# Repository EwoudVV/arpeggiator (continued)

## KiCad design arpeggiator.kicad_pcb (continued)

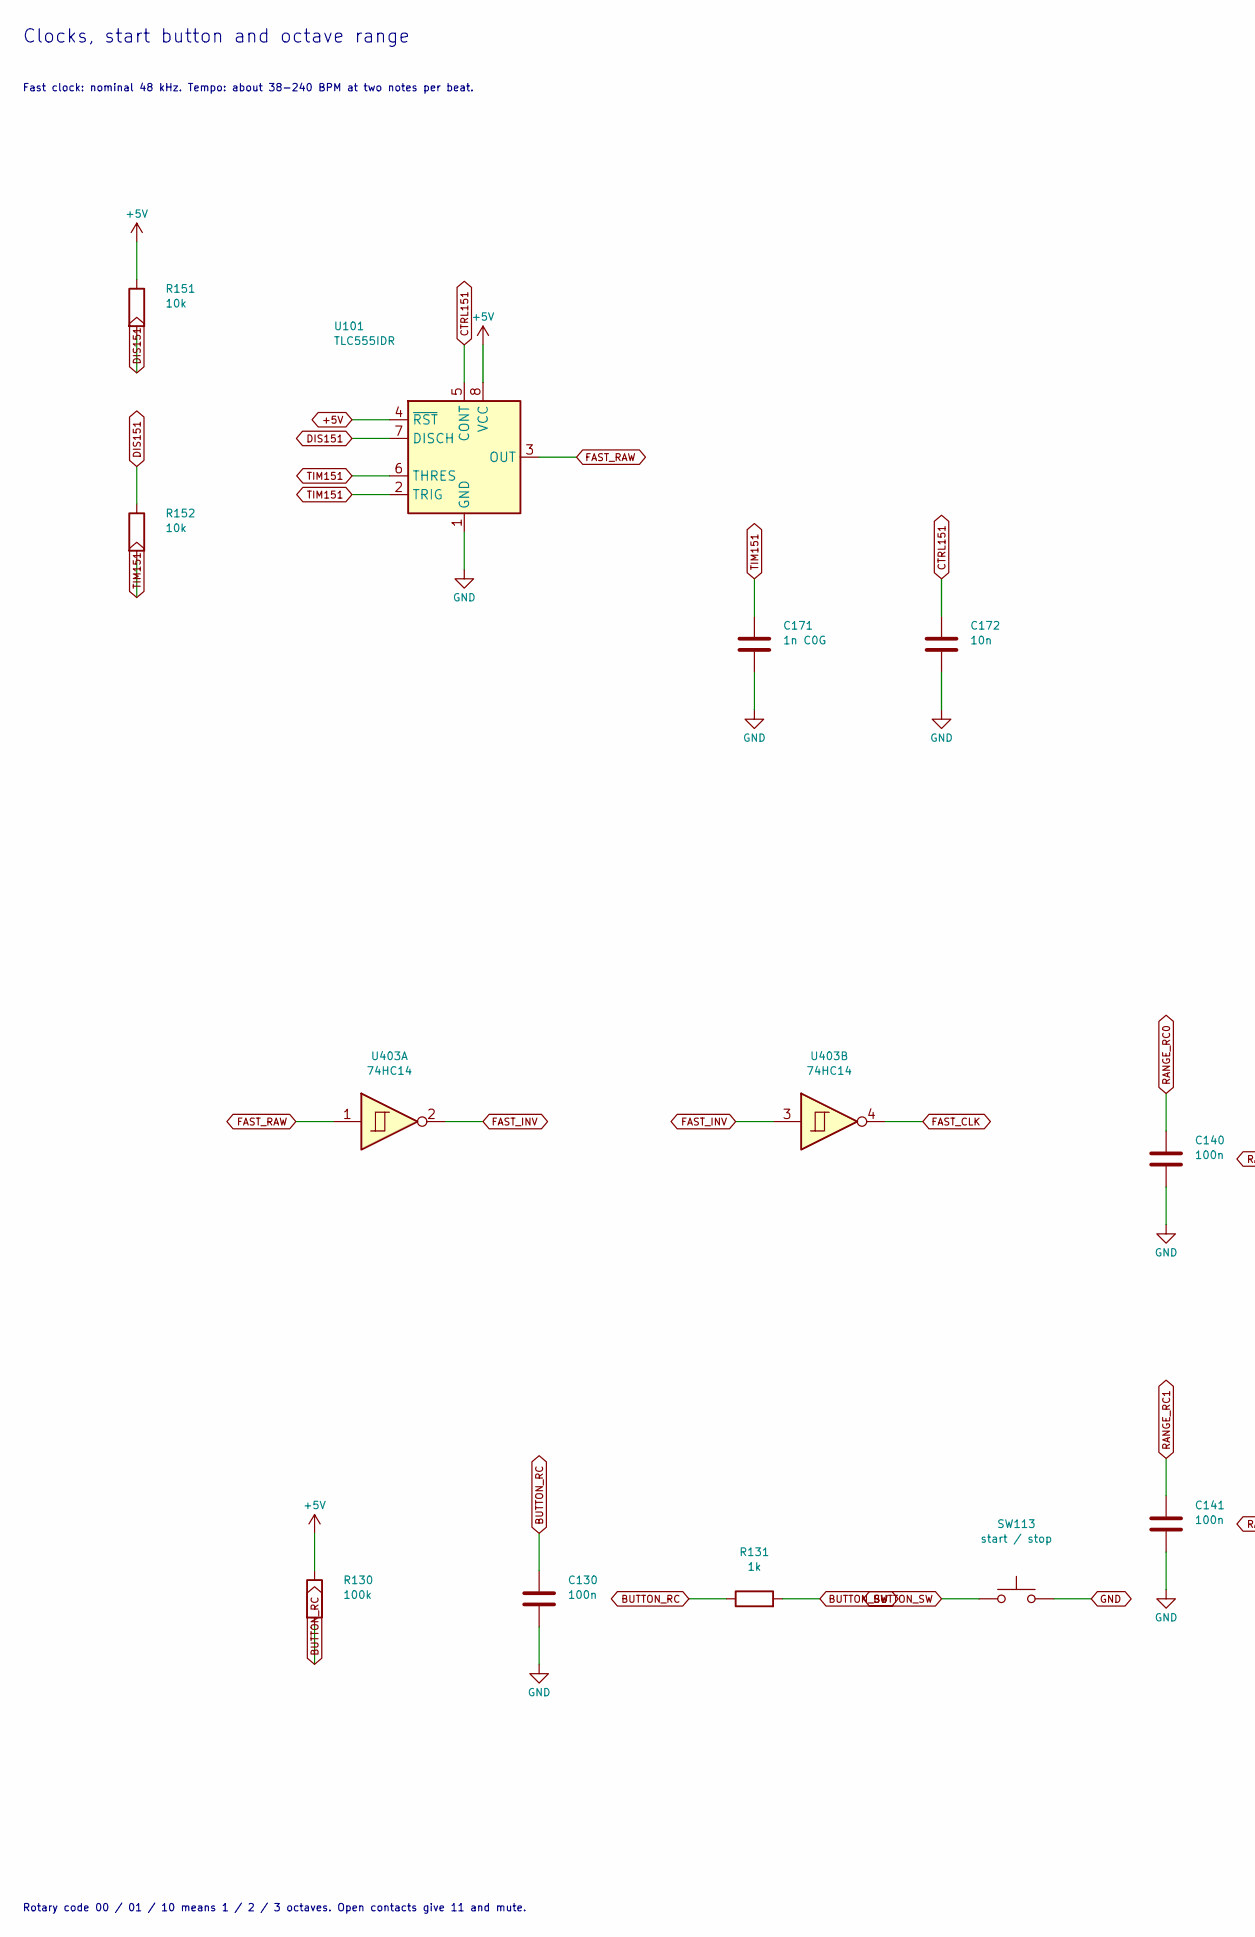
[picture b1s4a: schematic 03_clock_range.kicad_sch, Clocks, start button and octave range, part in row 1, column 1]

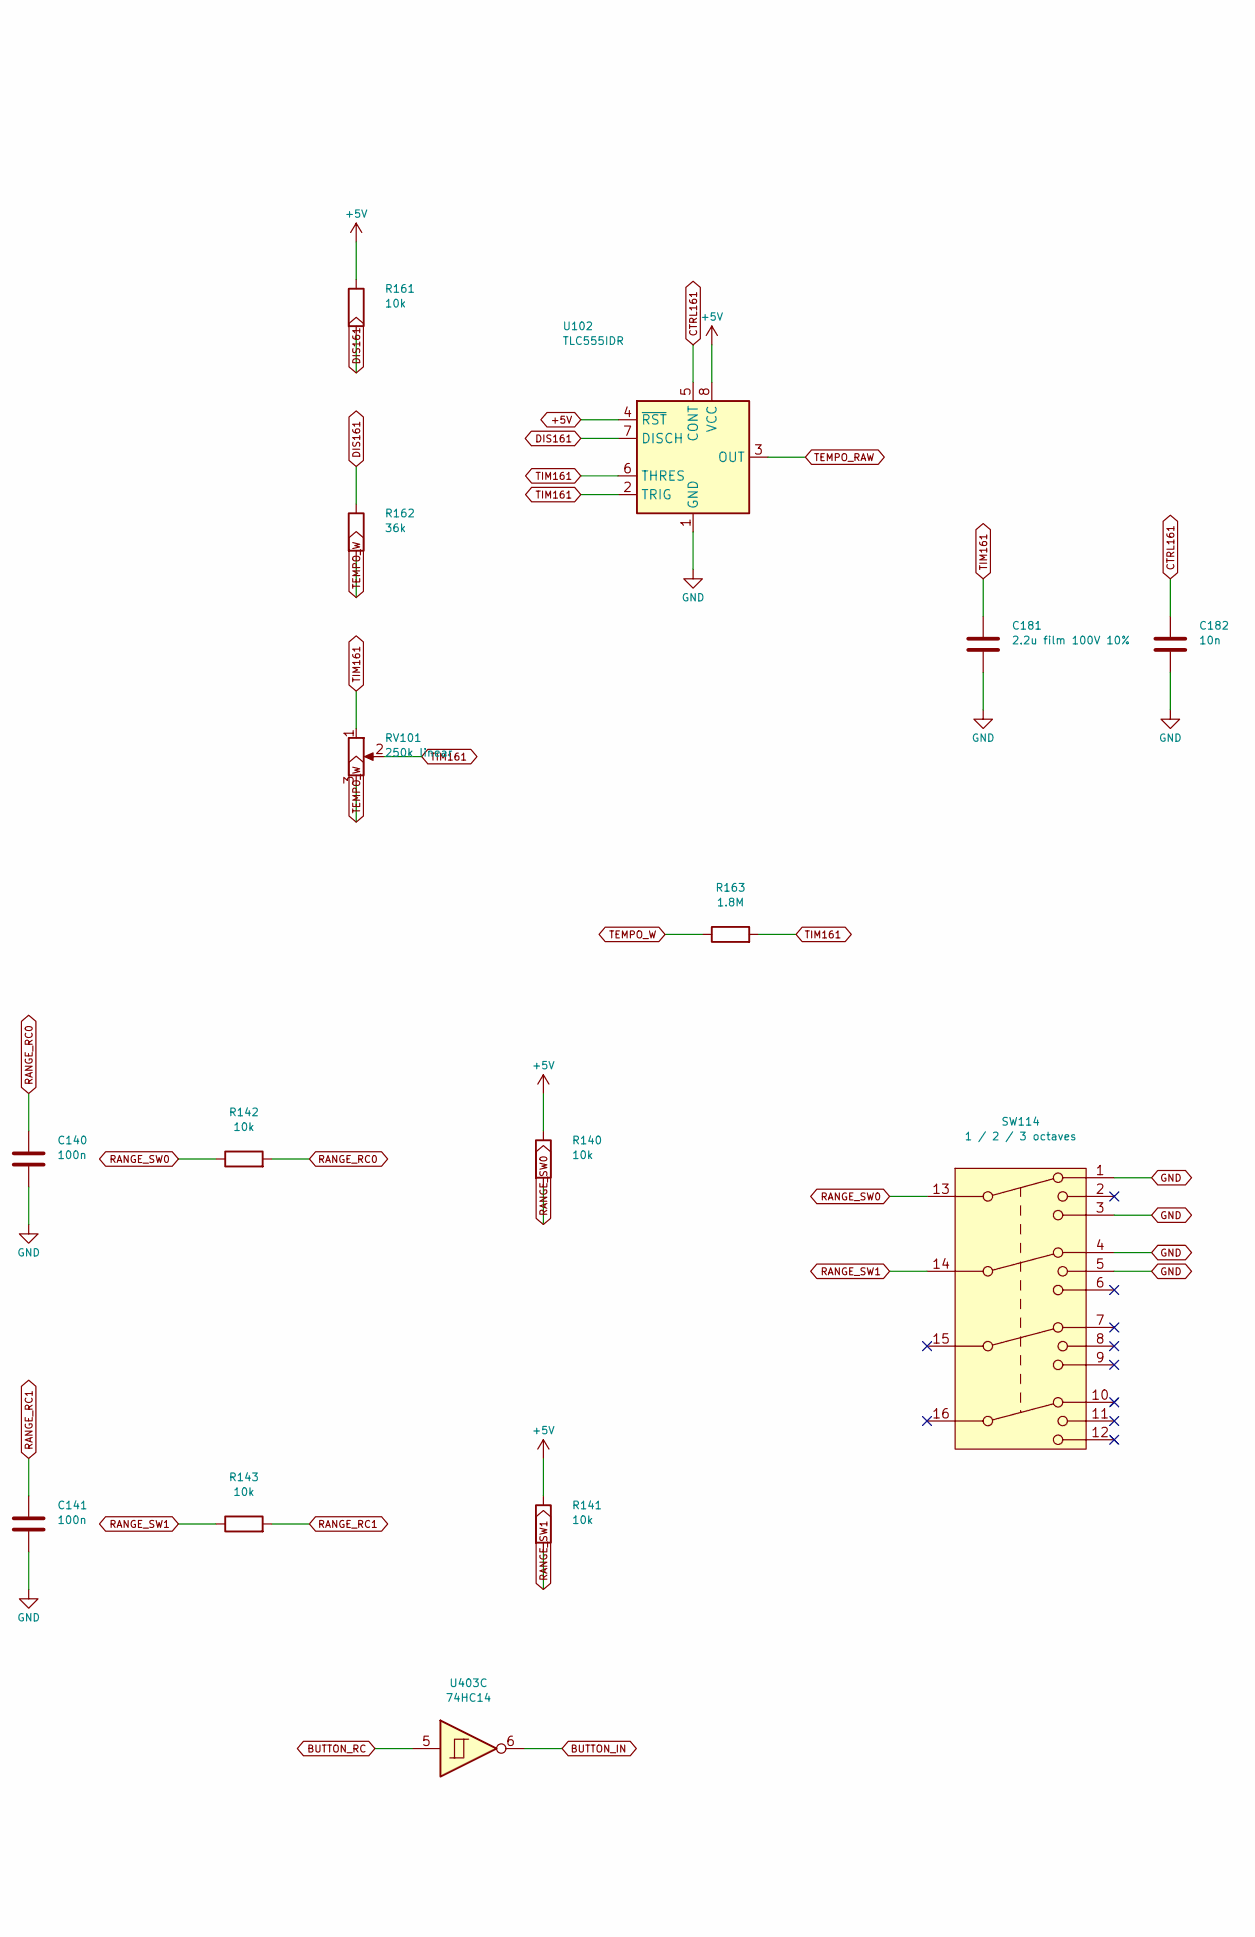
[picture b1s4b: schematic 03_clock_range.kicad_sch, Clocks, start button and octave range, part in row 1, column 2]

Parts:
C130, C140, C141: 100n; C_0805_2012Metric
C171: 1n C0G; C_0805_2012Metric
C172, C182: 10n; C_0805_2012Metric
C181: 2.2u film 100V 10%; C_Rect_L18.0mm_W8.0mm_P15.00mm_FKS3_FKP3; MPN MKS4D042204F00KSSD
R130: 100k; R_0805_2012Metric
R131: 1k; R_0805_2012Metric
R140, R141, R142, R143, R151, R152, R161: 10k; R_0805_2012Metric
R162: 36k; R_0805_2012Metric
R163: 1.8M; R_0805_2012Metric
RV101: 250k linear; Potentiometer_Alpha_RD901F-40-00D_Single_Vertical; MPN RD901F-40-15F-B250K
SW113: start / stop; SW_SPST_Omron_B3F-40xx; MPN B3F-4055
SW114: 1 / 2 / 3 octaves; SW_Alpha_SR2612F_4P3T; MPN SR2612F-0403-18R0B-D8-N
U101, U102: TLC555IDR; SOIC-8_3.9x4.9mm_P1.27mm; MPN TLC555IDR
U403: 74HC14; SOIC-14_3.9x8.7mm_P1.27mm; MPN 74HC14D,653

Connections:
+5V: R130.1, R140.1, R141.1, R151.1, R161.1, U101.4 (~RST), U101.8 (VCC), U102.4 (~RST), U102.8 (VCC); also elsewhere on the board
BUTTON_IN: U403.6; also elsewhere on the board
BUTTON_RC: C130.1, R130.2, R131.1, U403.5
BUTTON_SW: R131.2, SW113.1
CTRL151: C172.1, U101.5 (CONT)
CTRL161: C182.1, U102.5 (CONT)
DIS151: R151.2, R152.1, U101.7 (DISCH)
DIS161: R161.2, R162.1, U102.7 (DISCH)
FAST_CLK: U403.4; also elsewhere on the board
FAST_INV: U403.2, U403.3
FAST_RAW: U101.3 (OUT), U403.1
RANGE_RC0: C140.1, R142.2; also elsewhere on the board
RANGE_RC1: C141.1, R143.2; also elsewhere on the board
RANGE_SW0: R140.2, R142.1, SW114.13
RANGE_SW1: R141.2, R143.1, SW114.14
TEMPO_RAW: U102.3 (OUT); also elsewhere on the board
TEMPO_W: R162.2, R163.1, RV101.3
TIM151: C171.1, R152.2, U101.2 (TRIG), U101.6 (THRES)
TIM161: C181.1, R163.2, RV101.1, RV101.2, U102.2 (TRIG), U102.6 (THRES)

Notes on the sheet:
Clocks, start button and octave range
Fast clock: nominal 48 kHz. Tempo: about 38-240 BPM at two notes per beat.
Rotary code 00 / 01 / 10 means 1 / 2 / 3 octaves. Open contacts give 11 and mute.

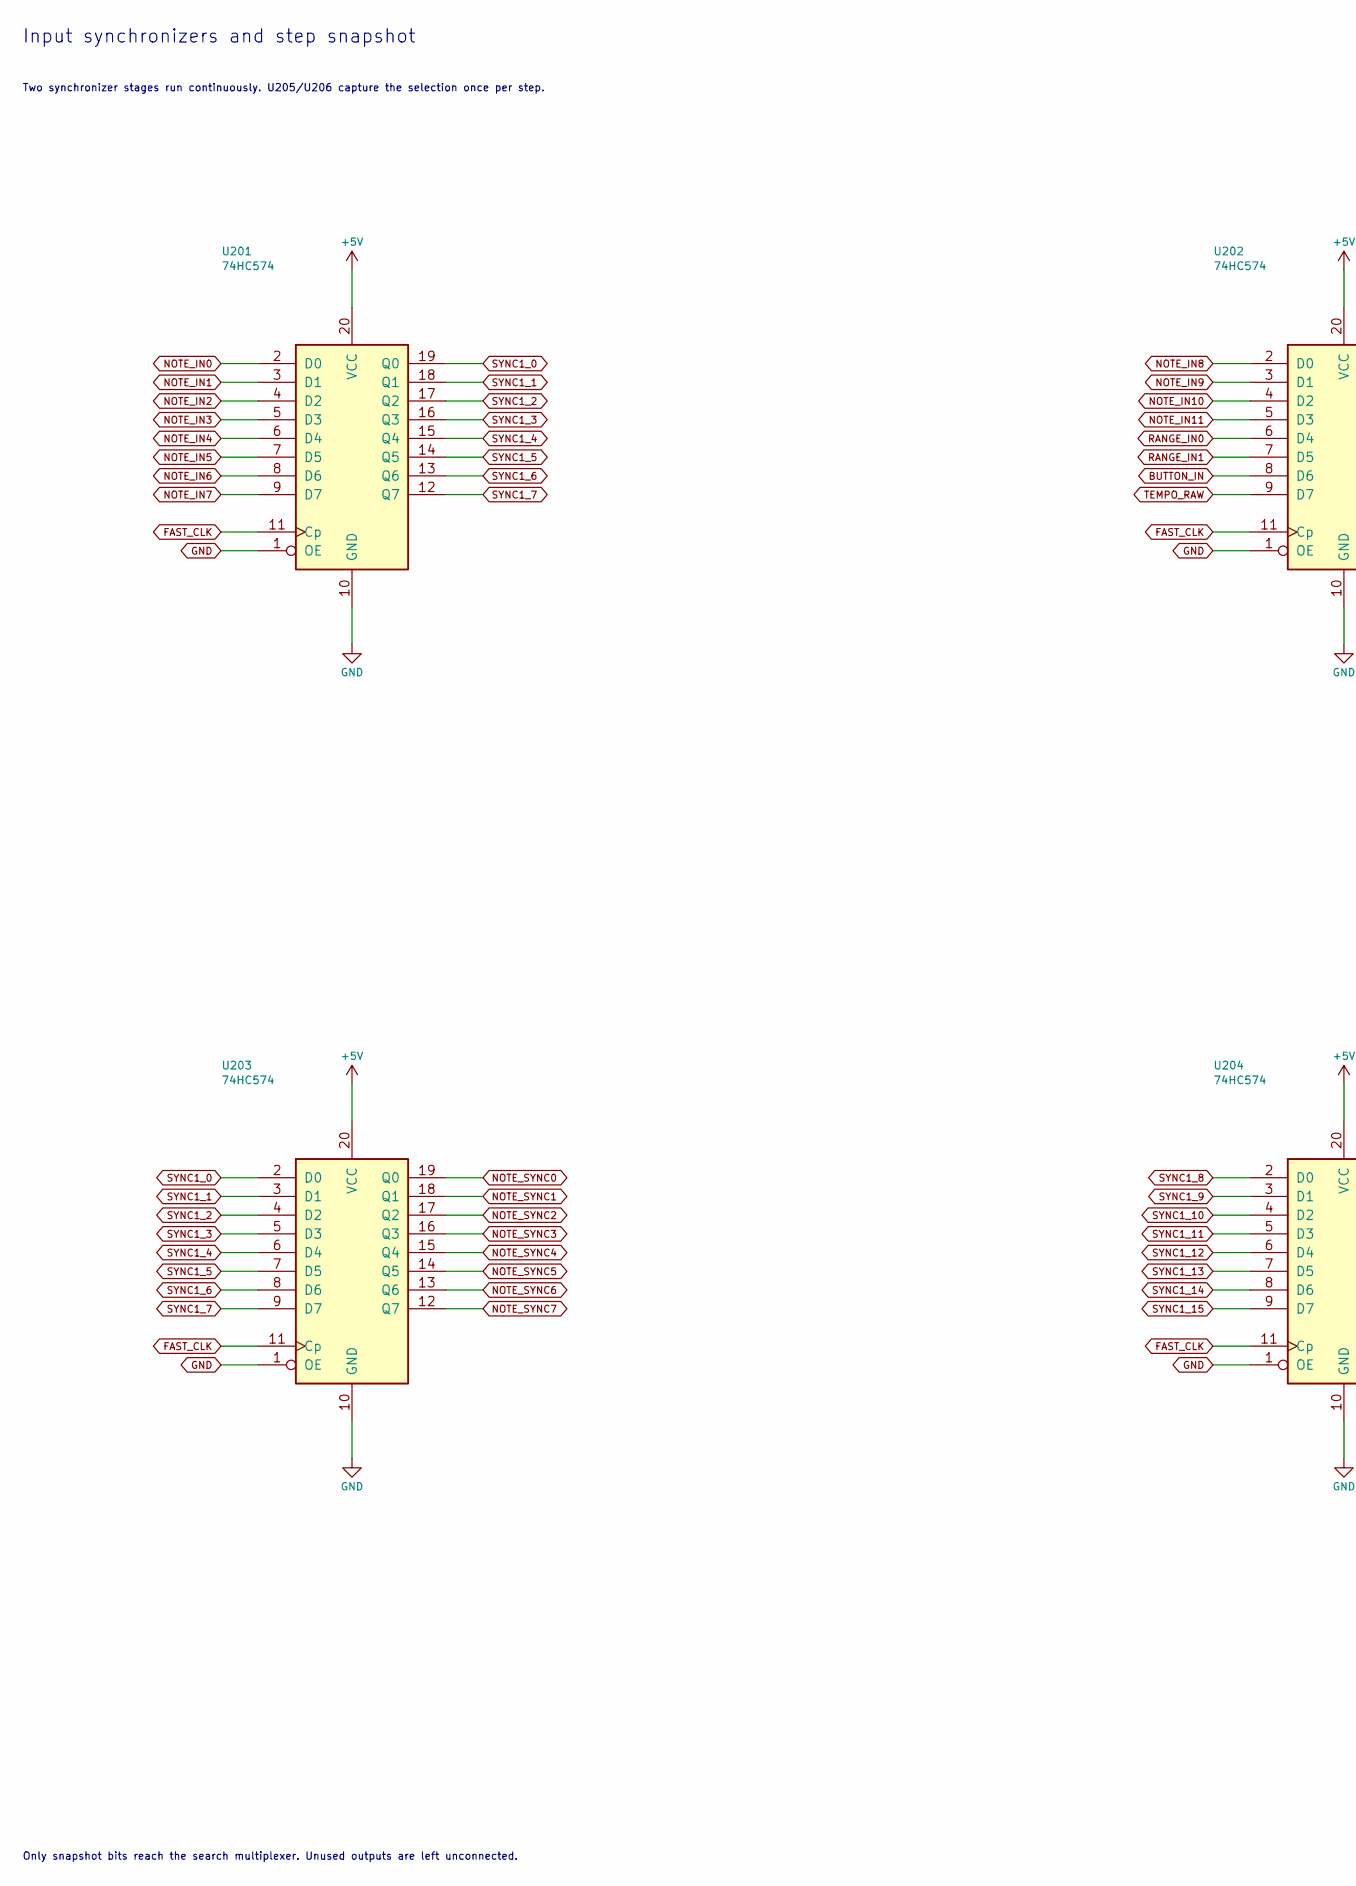
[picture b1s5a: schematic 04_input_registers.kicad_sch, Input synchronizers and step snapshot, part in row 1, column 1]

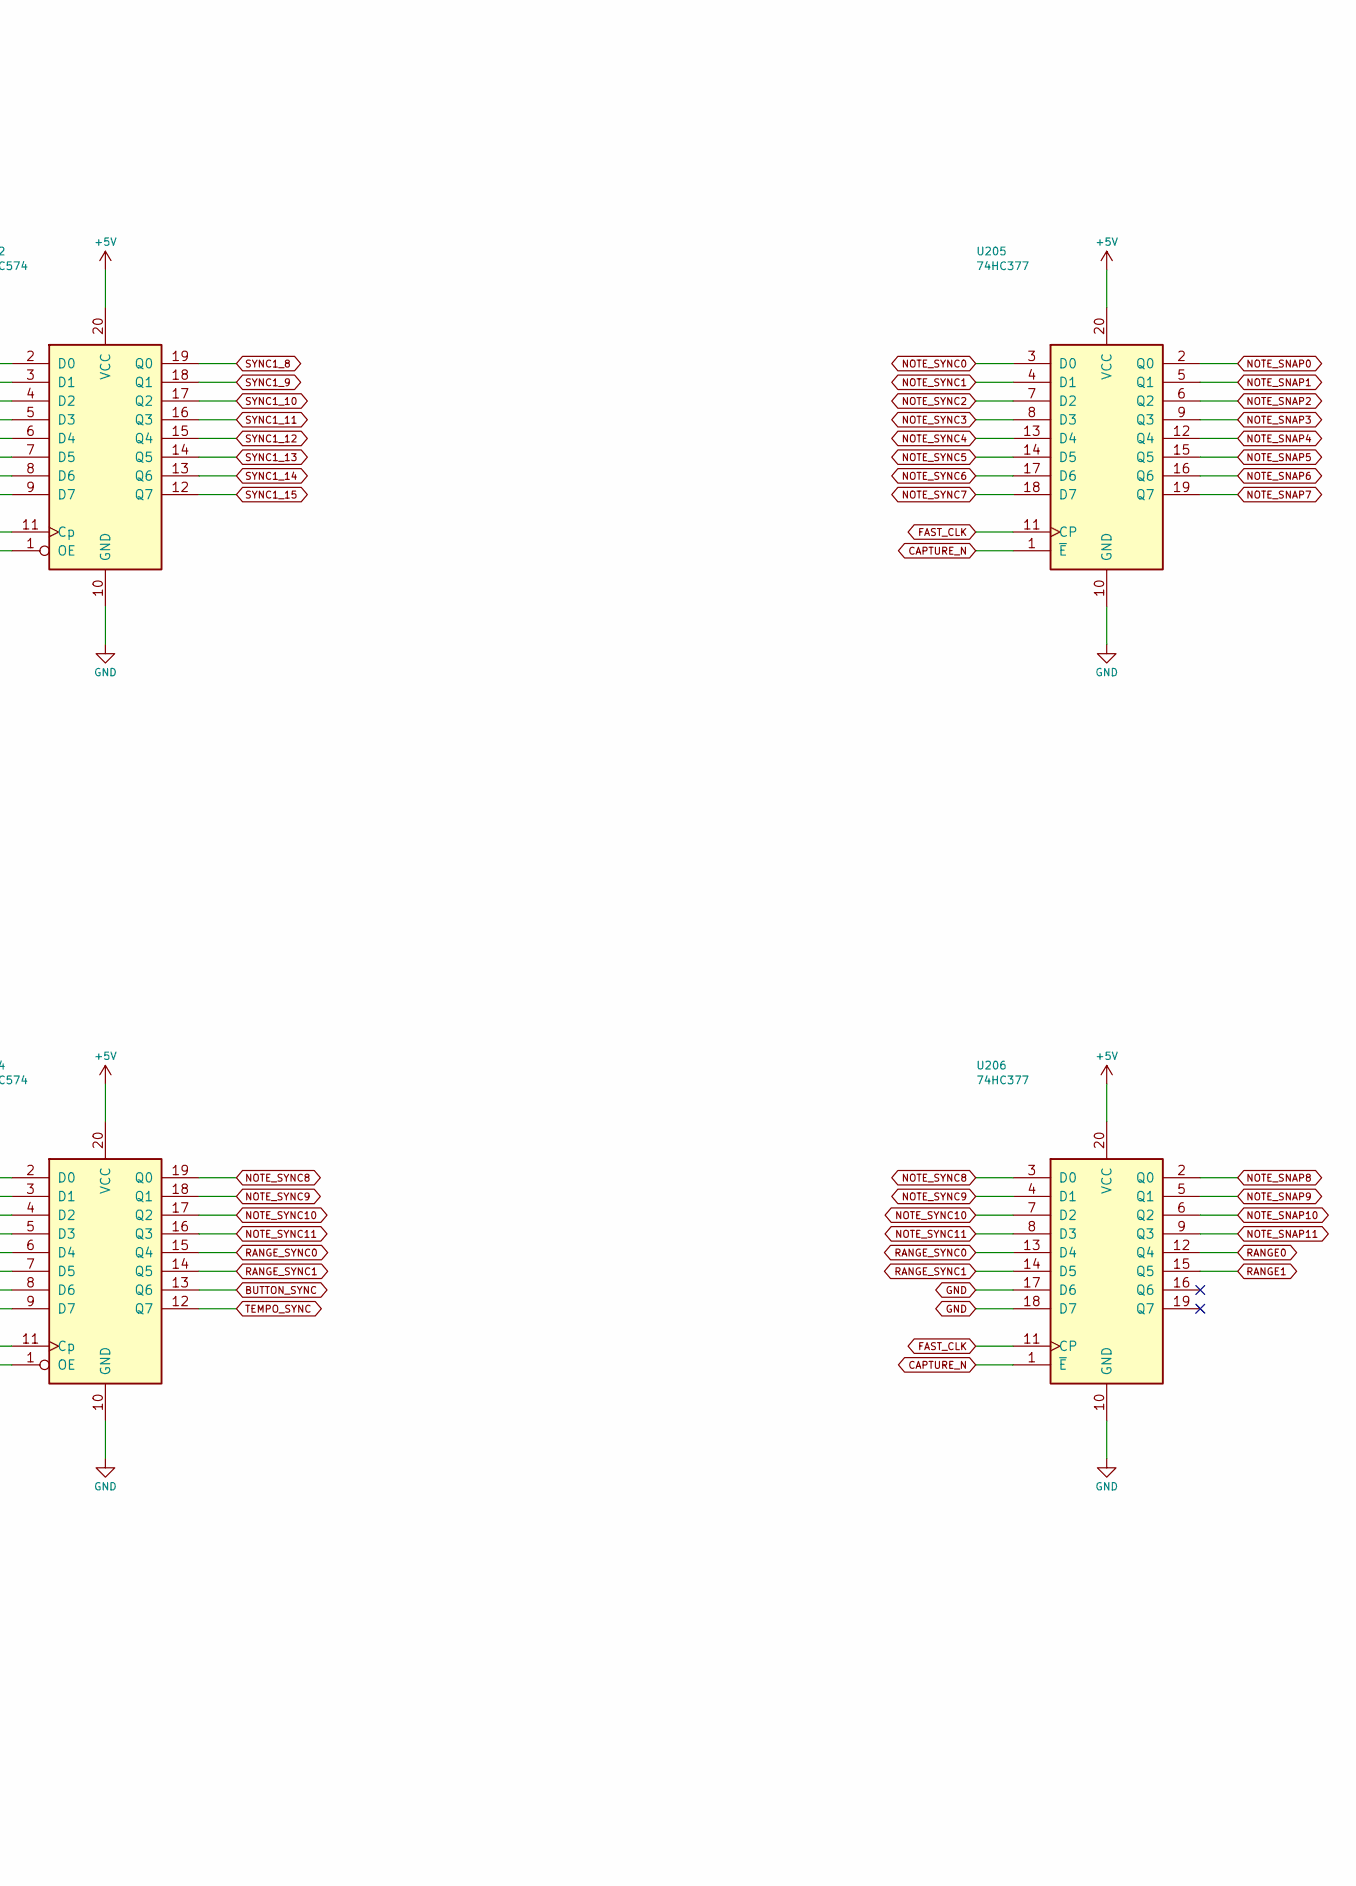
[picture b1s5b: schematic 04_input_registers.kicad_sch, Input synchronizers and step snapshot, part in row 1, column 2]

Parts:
U201, U202, U203, U204: 74HC574; SOIC-20W_7.5x12.8mm_P1.27mm; MPN 74HC574D,653
U205, U206: 74HC377; SOIC-20W_7.5x12.8mm_P1.27mm; MPN 74HC377D,653

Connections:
+5V: U201.20 (VCC), U202.20 (VCC), U203.20 (VCC), U204.20 (VCC), U205.20 (VCC), U206.20 (VCC); also elsewhere on the board
BUTTON_IN: U202.8 (D6); also elsewhere on the board
BUTTON_SYNC: U204.13 (Q6); also elsewhere on the board
CAPTURE_N: U205.1 (~E), U206.1 (~E); also elsewhere on the board
FAST_CLK: U201.11 (Cp), U202.11 (Cp), U203.11 (Cp), U204.11 (Cp), U205.11 (CP), U206.11 (CP); also elsewhere on the board
NOTE_IN0: U201.2 (D0); also elsewhere on the board
NOTE_IN1: U201.3 (D1); also elsewhere on the board
NOTE_IN2: U201.4 (D2); also elsewhere on the board
NOTE_IN3: U201.5 (D3); also elsewhere on the board
NOTE_IN4: U201.6 (D4); also elsewhere on the board
NOTE_IN5: U201.7 (D5); also elsewhere on the board
NOTE_IN6: U201.8 (D6); also elsewhere on the board
NOTE_IN7: U201.9 (D7); also elsewhere on the board
NOTE_IN8: U202.2 (D0); also elsewhere on the board
NOTE_IN9: U202.3 (D1); also elsewhere on the board
NOTE_IN10: U202.4 (D2); also elsewhere on the board
NOTE_IN11: U202.5 (D3); also elsewhere on the board
NOTE_SNAP0: U205.2 (Q0); also elsewhere on the board
NOTE_SNAP1: U205.5 (Q1); also elsewhere on the board
NOTE_SNAP2: U205.6 (Q2); also elsewhere on the board
NOTE_SNAP3: U205.9 (Q3); also elsewhere on the board
NOTE_SNAP4: U205.12 (Q4); also elsewhere on the board
NOTE_SNAP5: U205.15 (Q5); also elsewhere on the board
NOTE_SNAP6: U205.16 (Q6); also elsewhere on the board
NOTE_SNAP7: U205.19 (Q7); also elsewhere on the board
NOTE_SNAP8: U206.2 (Q0); also elsewhere on the board
NOTE_SNAP9: U206.5 (Q1); also elsewhere on the board
NOTE_SNAP10: U206.6 (Q2); also elsewhere on the board
NOTE_SNAP11: U206.9 (Q3); also elsewhere on the board
NOTE_SYNC0: U203.19 (Q0), U205.3 (D0)
NOTE_SYNC1: U203.18 (Q1), U205.4 (D1)
NOTE_SYNC2: U203.17 (Q2), U205.7 (D2)
NOTE_SYNC3: U203.16 (Q3), U205.8 (D3)
NOTE_SYNC4: U203.15 (Q4), U205.13 (D4)
NOTE_SYNC5: U203.14 (Q5), U205.14 (D5)
NOTE_SYNC6: U203.13 (Q6), U205.17 (D6)
NOTE_SYNC7: U203.12 (Q7), U205.18 (D7)
NOTE_SYNC8: U204.19 (Q0), U206.3 (D0)
NOTE_SYNC9: U204.18 (Q1), U206.4 (D1)
NOTE_SYNC10: U204.17 (Q2), U206.7 (D2)
NOTE_SYNC11: U204.16 (Q3), U206.8 (D3)
RANGE0: U206.12 (Q4); also elsewhere on the board
RANGE1: U206.15 (Q5); also elsewhere on the board
RANGE_IN0: U202.6 (D4); also elsewhere on the board
RANGE_IN1: U202.7 (D5); also elsewhere on the board
RANGE_SYNC0: U204.15 (Q4), U206.13 (D4)
RANGE_SYNC1: U204.14 (Q5), U206.14 (D5)
SYNC1_0: U201.19 (Q0), U203.2 (D0)
SYNC1_1: U201.18 (Q1), U203.3 (D1)
SYNC1_2: U201.17 (Q2), U203.4 (D2)
SYNC1_3: U201.16 (Q3), U203.5 (D3)
SYNC1_4: U201.15 (Q4), U203.6 (D4)
SYNC1_5: U201.14 (Q5), U203.7 (D5)
SYNC1_6: U201.13 (Q6), U203.8 (D6)
SYNC1_7: U201.12 (Q7), U203.9 (D7)
SYNC1_8: U202.19 (Q0), U204.2 (D0)
SYNC1_9: U202.18 (Q1), U204.3 (D1)
SYNC1_10: U202.17 (Q2), U204.4 (D2)
SYNC1_11: U202.16 (Q3), U204.5 (D3)
SYNC1_12: U202.15 (Q4), U204.6 (D4)
SYNC1_13: U202.14 (Q5), U204.7 (D5)
SYNC1_14: U202.13 (Q6), U204.8 (D6)
SYNC1_15: U202.12 (Q7), U204.9 (D7)
TEMPO_RAW: U202.9 (D7); also elsewhere on the board
TEMPO_SYNC: U204.12 (Q7); also elsewhere on the board

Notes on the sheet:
Input synchronizers and step snapshot
Two synchronizer stages run continuously. U205/U206 capture the selection once per step.
Only snapshot bits reach the search multiplexer. Unused outputs are left unconnected.

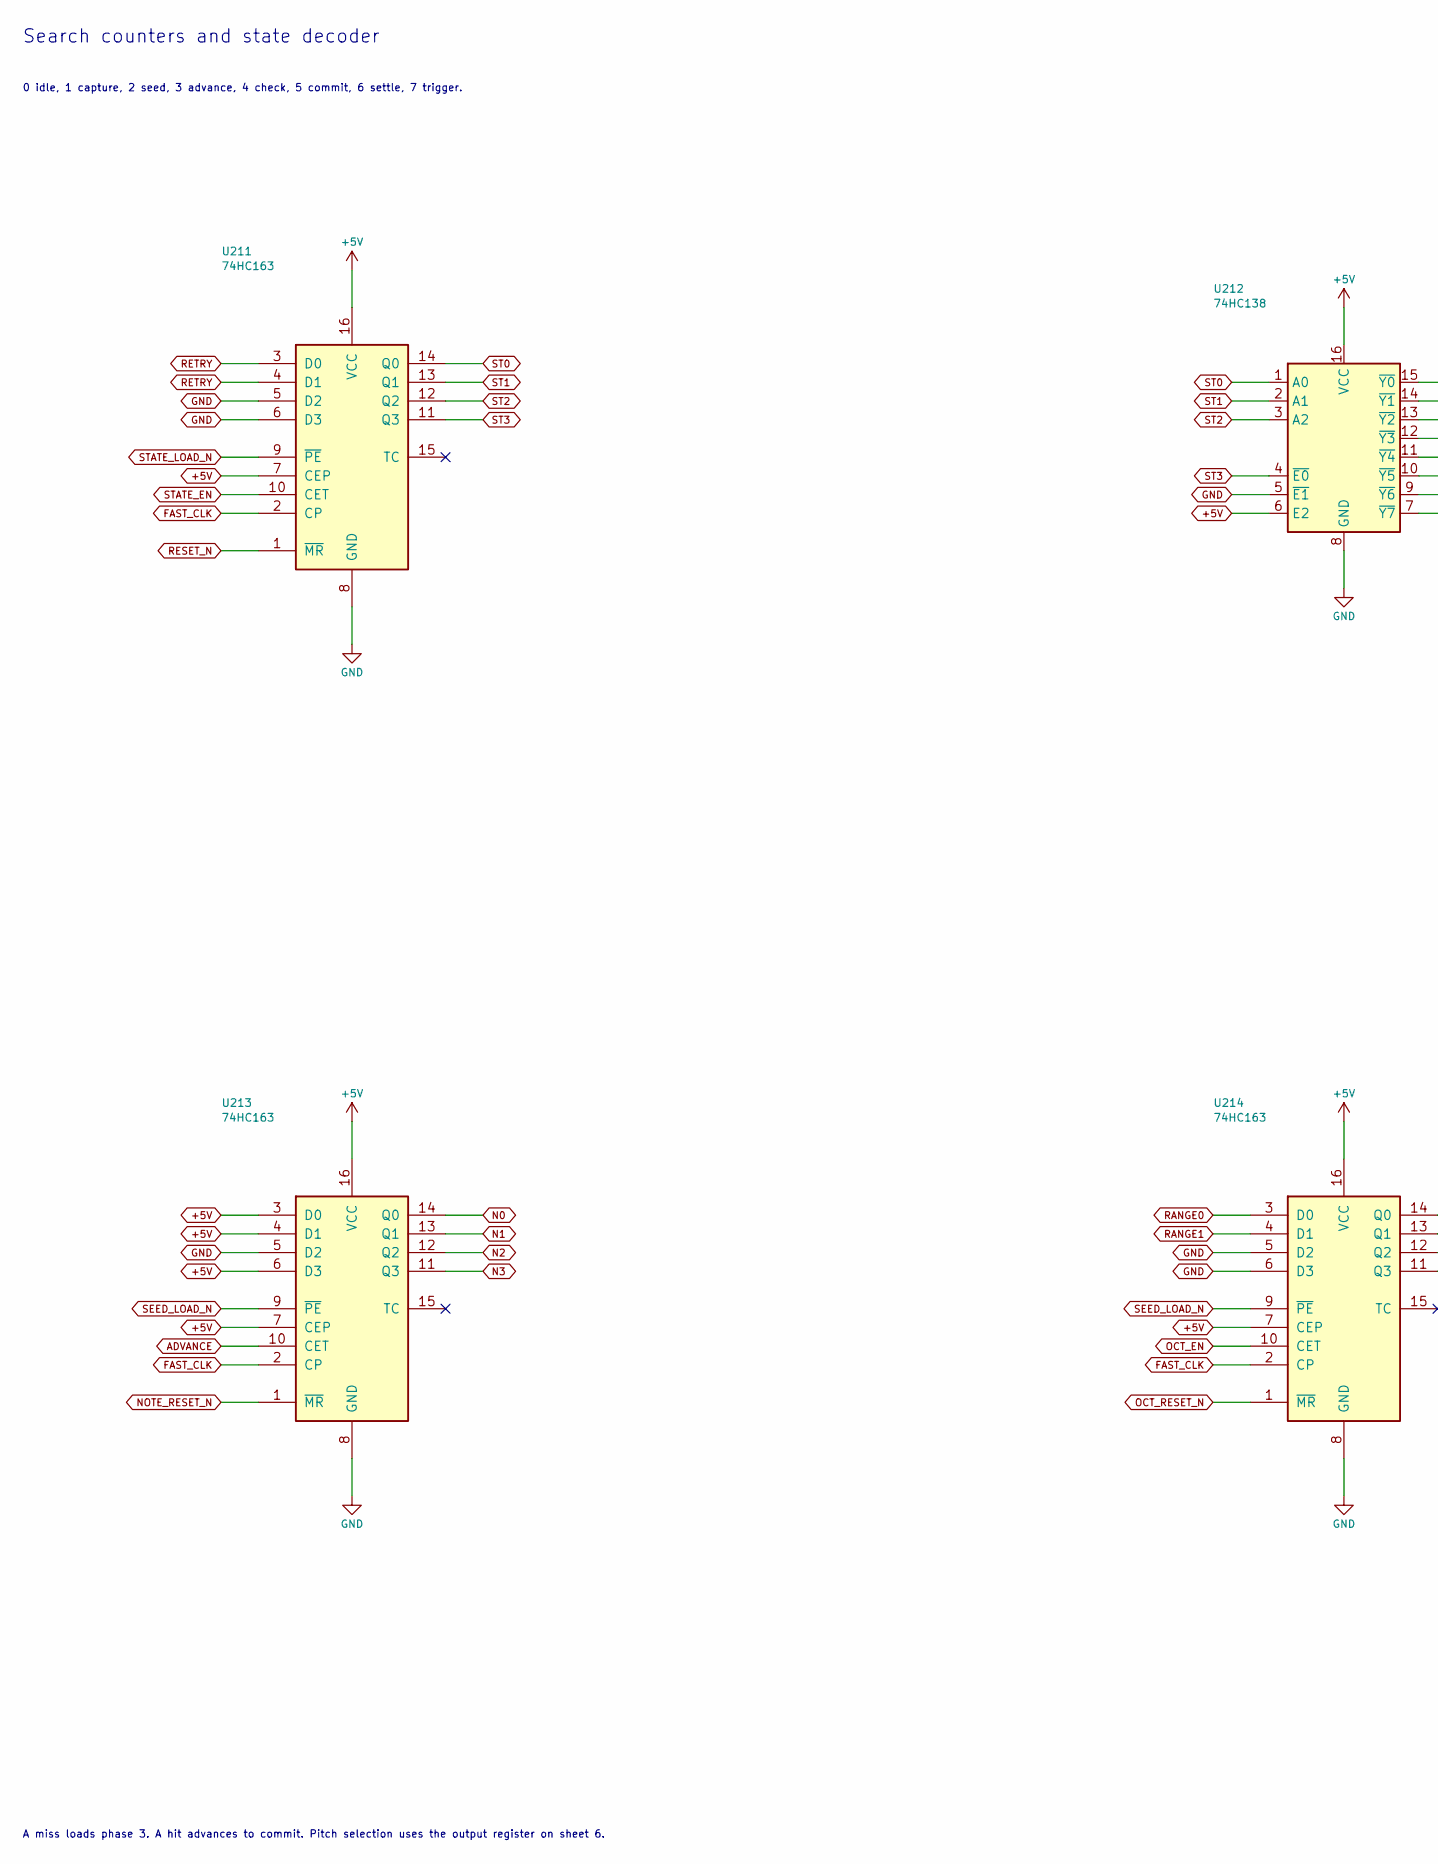
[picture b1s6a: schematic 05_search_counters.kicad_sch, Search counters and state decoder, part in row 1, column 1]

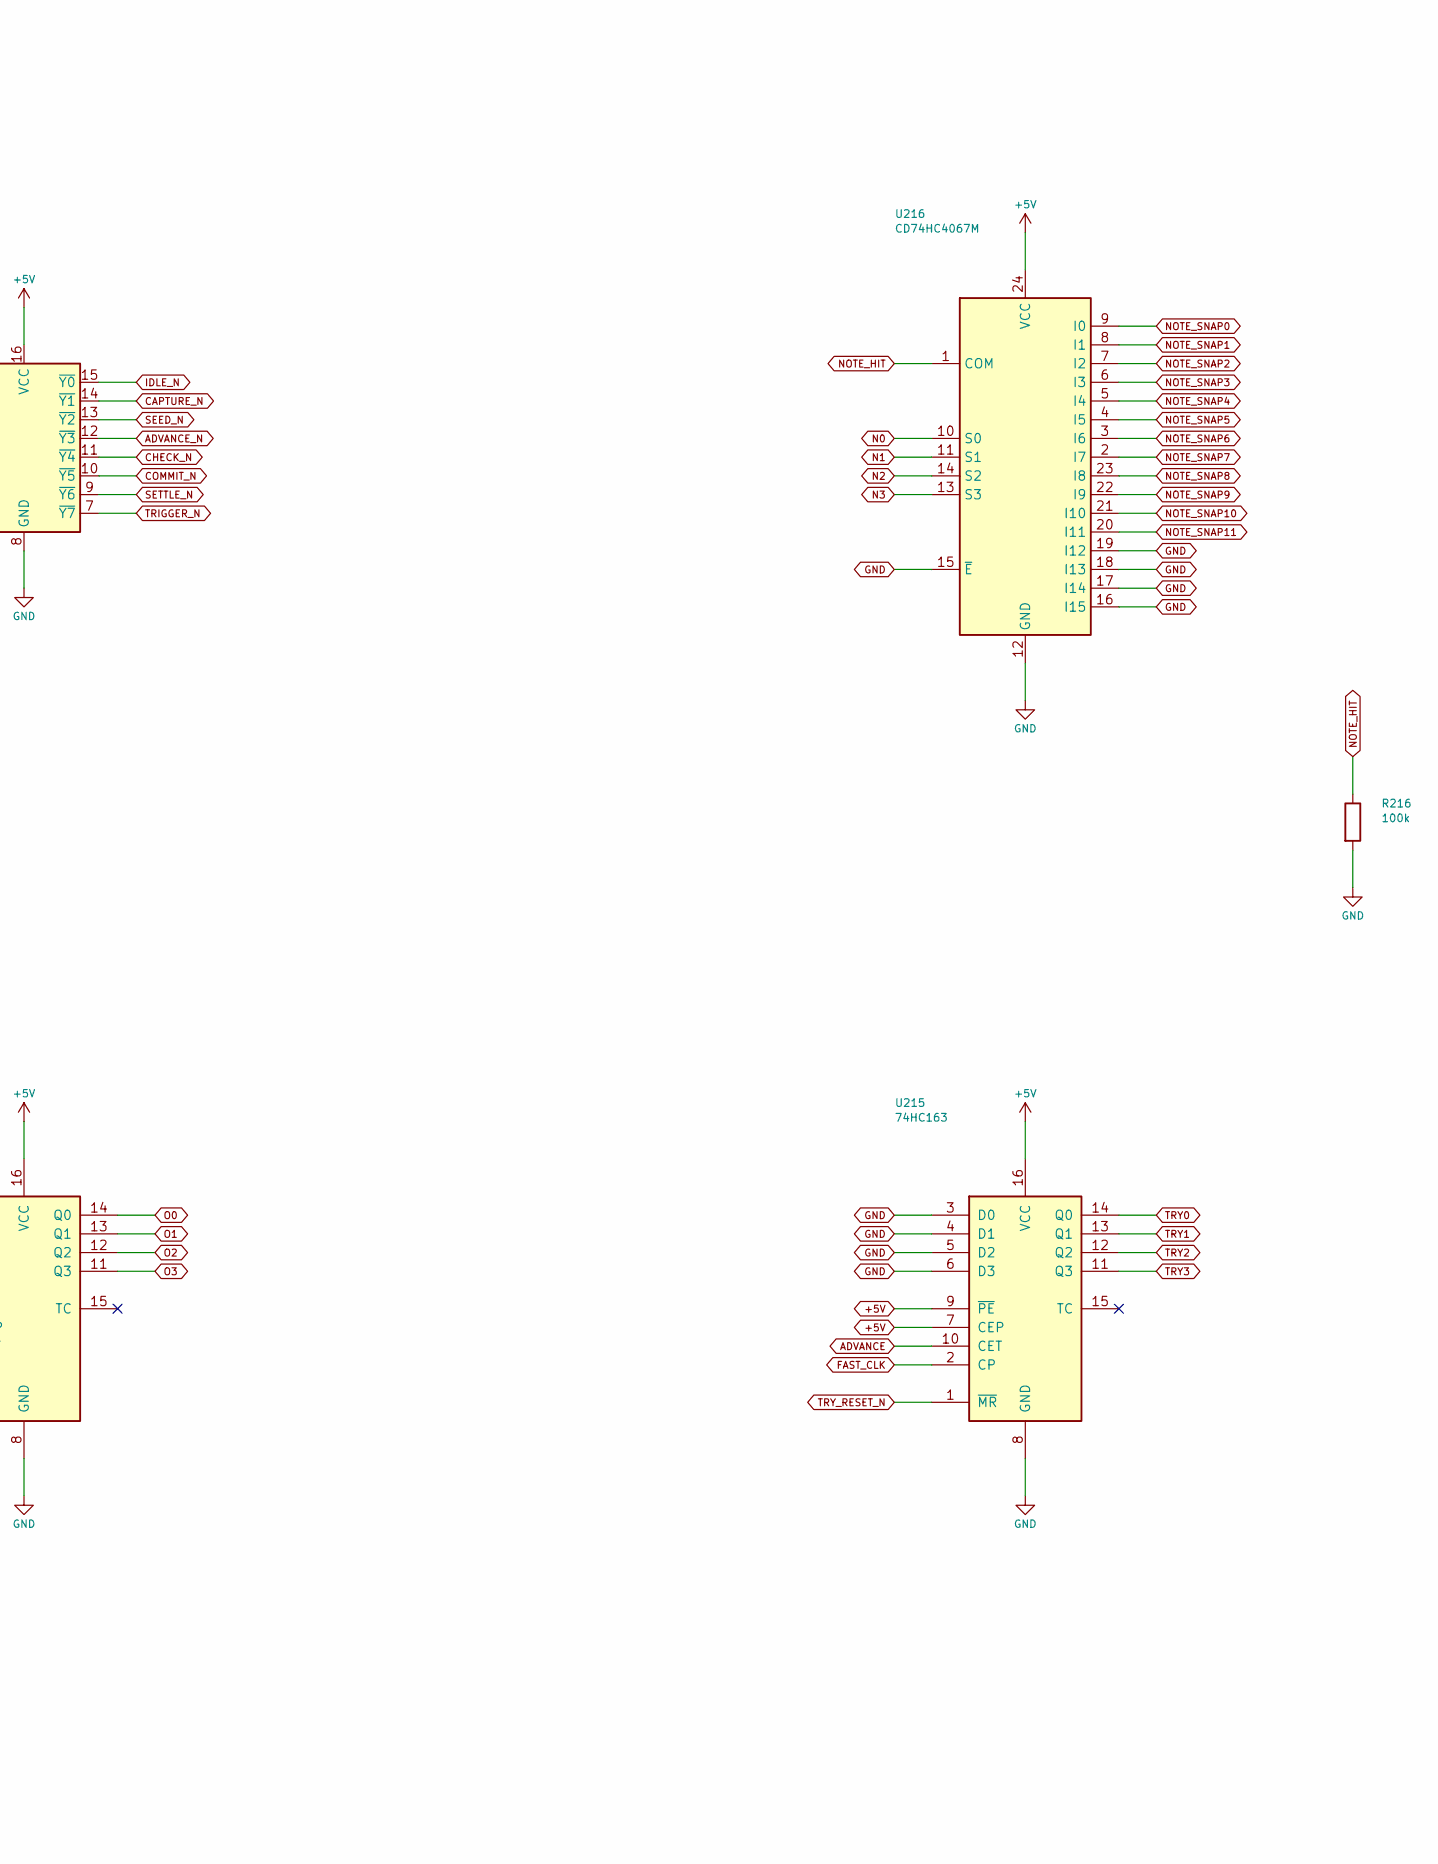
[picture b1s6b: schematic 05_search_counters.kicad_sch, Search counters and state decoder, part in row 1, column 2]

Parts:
R216: 100k; R_0805_2012Metric
U211, U213, U214, U215: 74HC163; SOIC-16_3.9x9.9mm_P1.27mm; MPN SN74HC163DR
U212: 74HC138; SOIC-16_3.9x9.9mm_P1.27mm; MPN 74HC138D,653
U216: CD74HC4067M; SOIC-24W_7.5x15.4mm_P1.27mm; MPN CD74HC4067M

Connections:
+5V: U211.7 (CEP), U211.16 (VCC), U212.6 (E2), U212.16 (VCC), U213.3 (D0), U213.4 (D1), U213.6 (D3), U213.7 (CEP), U213.16 (VCC), U214.7 (CEP), U214.16 (VCC), U215.7 (CEP), U215.9 (~PE), U215.16 (VCC), U216.24 (VCC); also elsewhere on the board
ADVANCE: U213.10 (CET), U215.10 (CET); also elsewhere on the board
ADVANCE_N: U212.12 (~Y3); also elsewhere on the board
CAPTURE_N: U212.14 (~Y1); also elsewhere on the board
CHECK_N: U212.11 (~Y4); also elsewhere on the board
COMMIT_N: U212.10 (~Y5); also elsewhere on the board
FAST_CLK: U211.2 (CP), U213.2 (CP), U214.2 (CP), U215.2 (CP); also elsewhere on the board
IDLE_N: U212.15 (~Y0); also elsewhere on the board
N0: U213.14 (Q0), U216.10 (S0); also elsewhere on the board
N1: U213.13 (Q1), U216.11 (S1); also elsewhere on the board
N2: U213.12 (Q2), U216.14 (S2); also elsewhere on the board
N3: U213.11 (Q3), U216.13 (S3); also elsewhere on the board
NOTE_HIT: R216.1, U216.1 (COM); also elsewhere on the board
NOTE_RESET_N: U213.1 (~MR); also elsewhere on the board
NOTE_SNAP0: U216.9 (I0); also elsewhere on the board
NOTE_SNAP1: U216.8 (I1); also elsewhere on the board
NOTE_SNAP2: U216.7 (I2); also elsewhere on the board
NOTE_SNAP3: U216.6 (I3); also elsewhere on the board
NOTE_SNAP4: U216.5 (I4); also elsewhere on the board
NOTE_SNAP5: U216.4 (I5); also elsewhere on the board
NOTE_SNAP6: U216.3 (I6); also elsewhere on the board
NOTE_SNAP7: U216.2 (I7); also elsewhere on the board
NOTE_SNAP8: U216.23 (I8); also elsewhere on the board
NOTE_SNAP9: U216.22 (I9); also elsewhere on the board
NOTE_SNAP10: U216.21 (I10); also elsewhere on the board
NOTE_SNAP11: U216.20 (I11); also elsewhere on the board
O0: U214.14 (Q0); also elsewhere on the board
O1: U214.13 (Q1); also elsewhere on the board
O2: U214.12 (Q2); also elsewhere on the board
O3: U214.11 (Q3); also elsewhere on the board
OCT_EN: U214.10 (CET); also elsewhere on the board
OCT_RESET_N: U214.1 (~MR); also elsewhere on the board
RANGE0: U214.3 (D0); also elsewhere on the board
RANGE1: U214.4 (D1); also elsewhere on the board
RESET_N: U211.1 (~MR); also elsewhere on the board
RETRY: U211.3 (D0), U211.4 (D1); also elsewhere on the board
SEED_LOAD_N: U213.9 (~PE), U214.9 (~PE); also elsewhere on the board
SEED_N: U212.13 (~Y2); also elsewhere on the board
SETTLE_N: U212.9 (~Y6); also elsewhere on the board
ST0: U211.14 (Q0), U212.1 (A0)
ST1: U211.13 (Q1), U212.2 (A1)
ST2: U211.12 (Q2), U212.3 (A2)
ST3: U211.11 (Q3), U212.4 (~E0); also elsewhere on the board
STATE_EN: U211.10 (CET); also elsewhere on the board
STATE_LOAD_N: U211.9 (~PE); also elsewhere on the board
TRIGGER_N: U212.7 (~Y7); also elsewhere on the board
TRY0: U215.14 (Q0); also elsewhere on the board
TRY1: U215.13 (Q1); also elsewhere on the board
TRY2: U215.12 (Q2); also elsewhere on the board
TRY3: U215.11 (Q3); also elsewhere on the board
TRY_RESET_N: U215.1 (~MR); also elsewhere on the board

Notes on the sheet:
Search counters and state decoder
0 idle, 1 capture, 2 seed, 3 advance, 4 check, 5 commit, 6 settle, 7 trigger.
A miss loads phase 3. A hit advances to commit. Pitch selection uses the output register on sheet 6.
